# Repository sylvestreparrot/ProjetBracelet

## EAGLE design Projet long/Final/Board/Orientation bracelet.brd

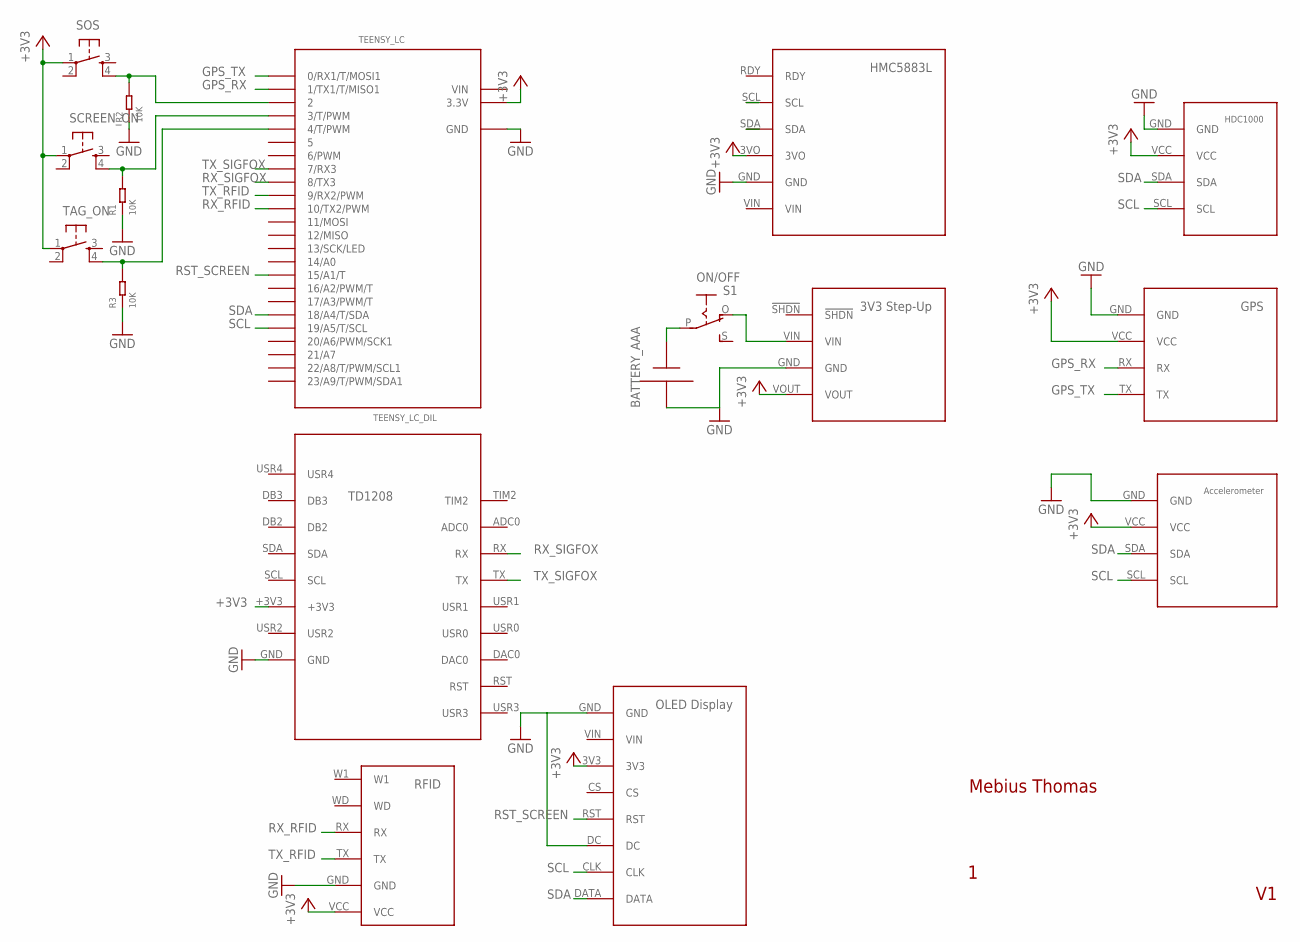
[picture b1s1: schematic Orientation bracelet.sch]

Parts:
BATTERY_AAA: AAA; 12BH412
ON/OFF: S1; EG1218
R1, R2, R3: 10K; PR-D2.3XL6.5MM
SCREEN_ON: TAC_SWITCHPTH; TACTILE-PTH
SOS: TAC_SWITCHPTH; TACTILE-PTH
TAG_ON: TAC_SWITCHPTH; TACTILE-PTH
TEENSY_LC: TEENSY_LC_DIL; TEENSY_3.0-3.2&LC_DIL
U$1: OLED_DISPLAY
U$2: RFID"; RFID
U$3: 3V3_STEP-UP
U$4: ACCELEROMETER
U$5: HDC1000
U$6: GPS
U$7: HMC5883L
U$8: TD1208

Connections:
+3V3: SCREEN_ON.1, SOS.1, TAG_ON.1, TEENSY_LC.3.3V, U$1.3V3, U$2.VCC, U$3.VOUT, U$4.VCC, U$5.VCC, U$6.VCC, U$7.3VO, U$8.+3V3
GND: BATTERY_AAA.-, R1.1, R2.1, R3.1, TEENSY_LC.AGND (GND), TEENSY_LC.GND, U$1.DC, U$1.GND, U$2.GND, U$3.GND, U$4.GND, U$5.GND, U$6.GND, U$7.GND, U$8.GND
GPS_RX: TEENSY_LC.1 (1/TX1/T/MISO1), U$6.RX
GPS_TX: TEENSY_LC.0 (0/RX1/T/MOSI1), U$6.TX
unnamed: R2.2, SOS.4, TEENSY_LC.2
unnamed: R1.2, SCREEN_ON.4, TEENSY_LC.3 (3/T/PWM)
unnamed: R3.2, TAG_ON.4, TEENSY_LC.4 (4/T/PWM)
unnamed: BATTERY_AAA.+, ON/OFF.P
unnamed: ON/OFF.O, U$3.VIN
RST_SCREEN: TEENSY_LC.15/A1 (15/A1/T), U$1.RST
RX_RFID: TEENSY_LC.10 (10/TX2/PWM), U$2.RX
RX_SIGFOX: TEENSY_LC.8 (8/TX3), U$8.RX
SCL: TEENSY_LC.19/A5 (19/A5/T/SCL), U$1.CLK, U$4.SCL, U$5.SCL, U$7.SCL
SDA: TEENSY_LC.18/A4 (18/A4/T/SDA), U$1.DATA, U$4.SDA, U$5.SDA, U$7.SDA
TX_RFID: TEENSY_LC.9 (9/RX2/PWM), U$2.TX
TX_SIGFOX: TEENSY_LC.7 (7/RX3), U$8.TX
VIN: TEENSY_LC.VIN

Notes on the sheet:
Mebius Thomas

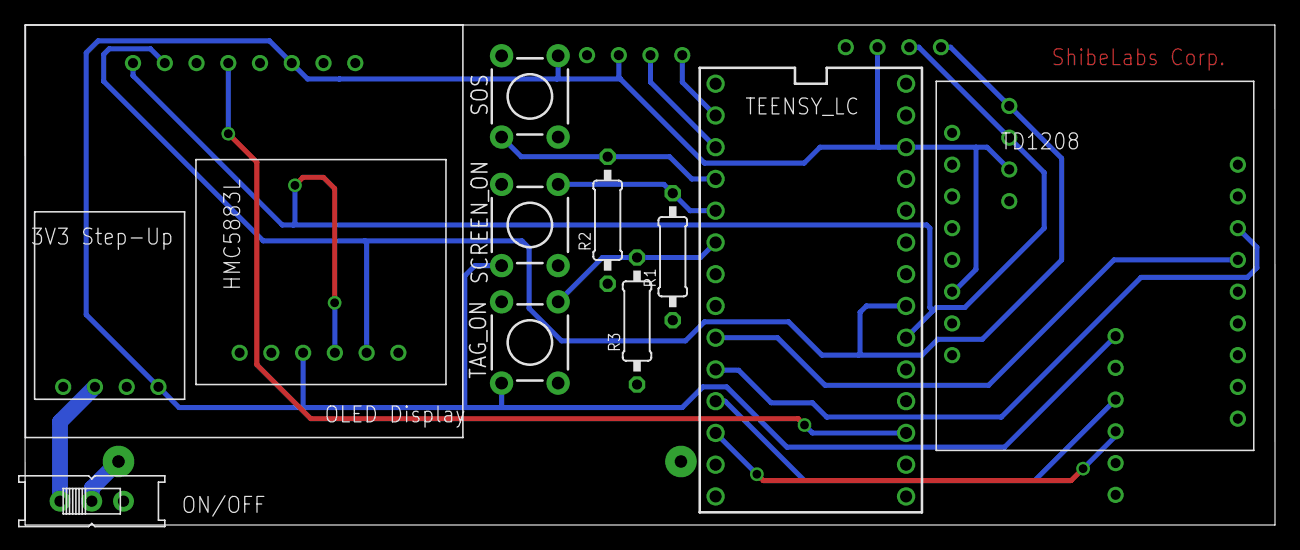
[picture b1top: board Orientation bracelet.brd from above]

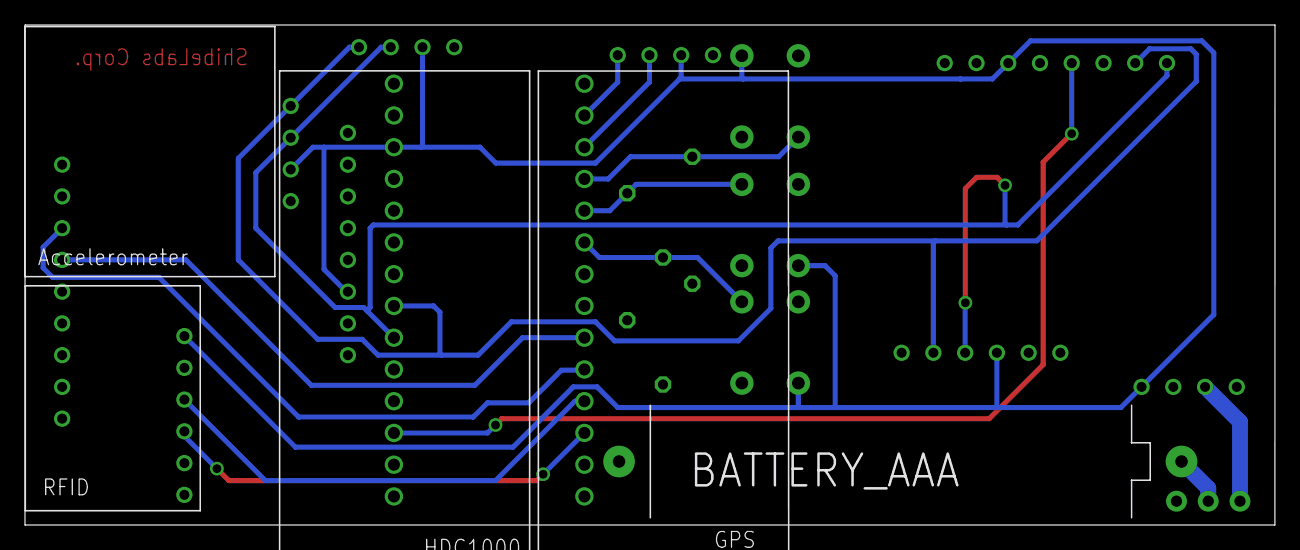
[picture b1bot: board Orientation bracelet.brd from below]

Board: 2 copper layers, 100.0 x 40.0 mm, 17 parts (5 on the bottom side), 16 nets.

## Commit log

2017-02-01 test
2017-02-01 Revert "Commit"
    This reverts commit 1fa2e5d36f8c8570219f25c2f9453edeacaeefd2.
2017-02-05 Change

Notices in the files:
parts and their libraries:
SparkFun: Licensing: CC v3.0 Share-Alike You are welcome to use this library for commercial purposes.
